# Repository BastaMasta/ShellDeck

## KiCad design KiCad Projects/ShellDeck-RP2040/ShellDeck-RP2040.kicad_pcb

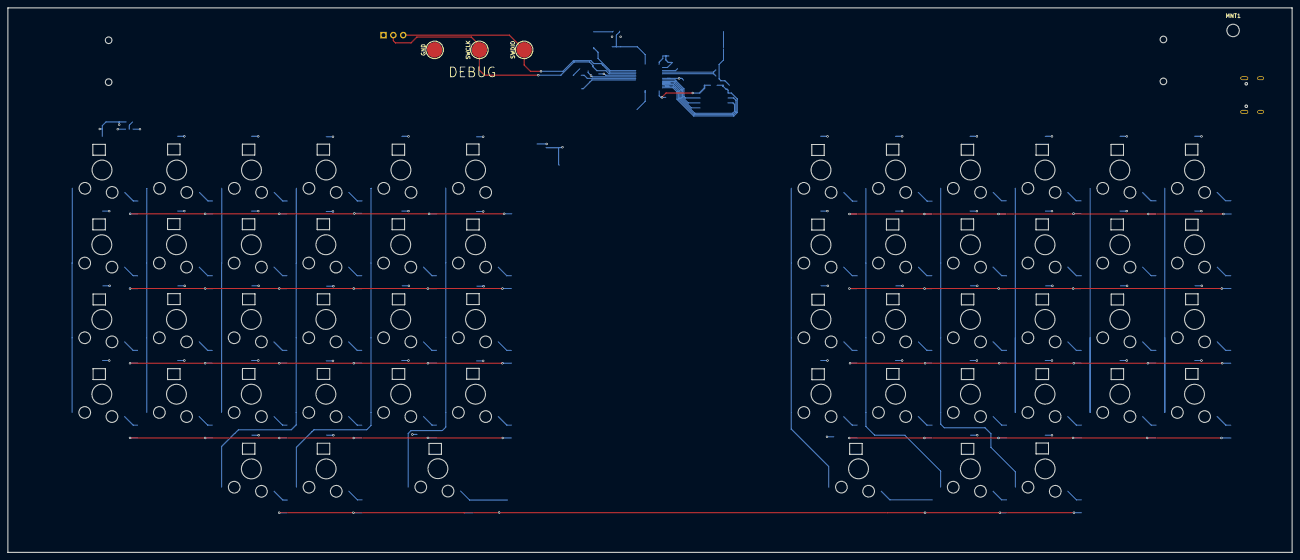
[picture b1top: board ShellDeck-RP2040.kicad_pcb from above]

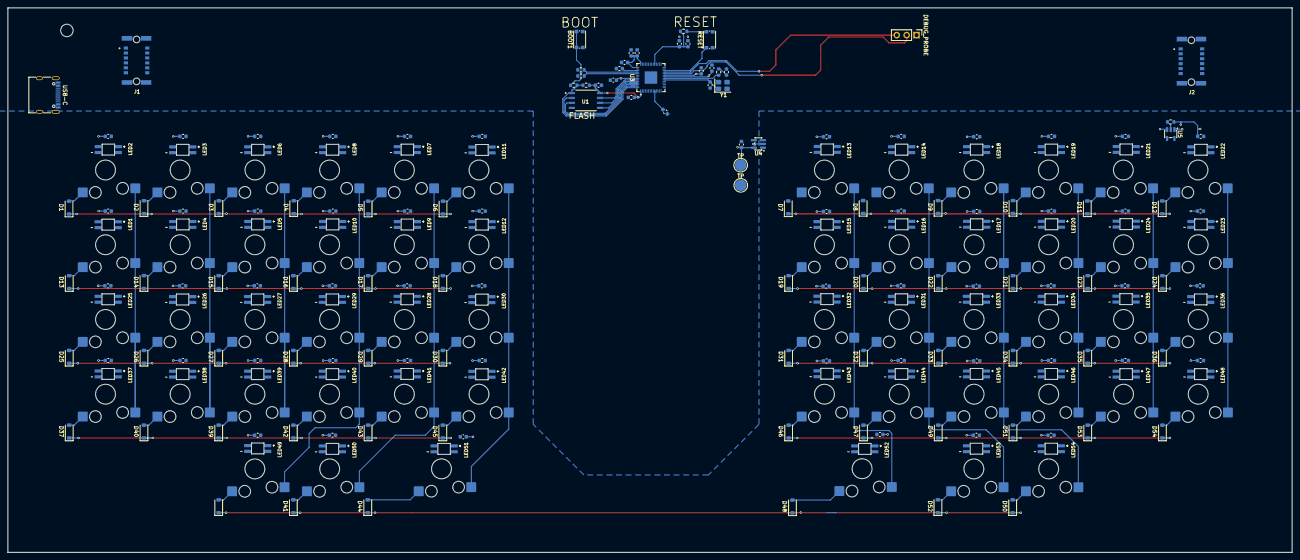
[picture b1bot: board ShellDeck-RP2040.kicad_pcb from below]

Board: 2 copper layers, 330.0 x 139.9 mm, 255 parts (251 on the bottom side), 39 nets.

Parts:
BOOT1: SW_Push_1P1T-KMR2; SW_Push_1P1T_NO_CK_KMR2
C1, C2, C3, C4, C9, C10, C12, C14, C15, C16, C17, C19: 0.1uF; C_0603_1608Metric
C12#2: 15pF; C_0603_1608Metric
C20: 12pF; C_0603_1608Metric
C21, C22, C23, C24, C25, C26, C27, C28, C29, C30, C31, C32, C33, C34, C35, C36, C37, C38, C39, C40, C41, C42, C43, C44, C45, C46, C47, C48, C49, C50, C51, C52, C53, C54, C55, C56, C57, C58, C59, C60, C61, C62, C63, C64, C65, C66, C67, C68, C69, C70, C71, C72, C73, C74, C75: C_0603; C_0603_1608Metric
D1, D2, D3, D4, D5, D6, D7, D8, D9, D10, D11, D12, D13, D14, D15, D16, D17, D18, D19, D20, D21, D22, D23, D24, D25, D26, D27, D28, D29, D30, D31, D32, D33, D34, D35, D36, D37, D38, D39, D40, D41, D42, D43, D44, D45, D46, D47, D48, D49, D50, D51, D52, D53, D54: 1N4148W; D_SOD-123
DEBUG_PROBE: PinHeader_1x03_P2.54mm_Vertical
GND: TestPoint_Pad_D4.0mm
J1, J2: M55-6001242R; HARWIN_M55-6001242R_vf.oMBanTfeTFaffFJxKZthsg
LED1, LED2, LED3, LED4, LED5, LED6, LED7, LED8, LED9, LED10, LED11, LED12, LED13, LED14, LED15, LED16, LED17, LED18, LED19, LED20, LED21, LED22, LED23, LED24, LED25, LED26, LED27, LED28, LED29, LED30, LED31, LED32, LED33, LED34, LED35, LED36, LED37, LED38, LED39, LED40, LED41, LED42, LED43, LED44, LED45, LED46, LED47, LED48, LED49, LED50, LED51, LED52, LED53, LED54: SK6812-EJ; LED_SK6812-E_vf.Ervw3JzPTGmCGe0GRPVqiQ
MNT1: MountingHole_3.2mm_M3_DIN965
R1, R4, R8: R_0603; R_0603_1608Metric
R2, R6: 1K; R_0603_1608Metric
R3, R5: 10K; R_0603_1608Metric
RESET: SW_Push_1P1T-KMR2; SW_Push_1P1T_NO_CK_KMR2
SW1, SW2, SW3, SW4, SW5, SW6, SW7, SW8, SW9, SW10, SW11, SW12, SW13, SW14, SW15, SW16, SW17, SW18, SW19, SW20, SW21, SW22, SW23, SW24, SW25, SW26, SW27, SW28, SW29, SW30, SW31, SW32, SW33, SW34, SW35, SW36, SW37, SW38, SW39, SW40, SW41, SW42, SW43, SW44, SW45, SW46, SW47, SW48, SW49, SW50, SW53, SW54: 1U; Gateron-KS33-Hotswap-1U
SW52, SW52#2: 2U; Gateron-KS33-Hotswap-2U
SWCLK: TestPoint_Pad_D4.0mm
SWDIO: TestPoint_Pad_D4.0mm
TP: TestPoint_Pad_D3.0mm
TP#2: TestPoint_Pad_D3.0mm
U1: W25Q128JVSIM_TR; SOIC127P790X216-8N_vf.sZCPWVPXQH2F8wQTRRFyVA
U3: QFN-56-1EP_7x7mm_P0.4mm_EP3.2x3.2mm
U4: AP2112K-3.3TRG1; SC-74A-5_1.55x2.9mm_P0.95mm
U5: SOT-23-5
USB-C: USB_C_Receptacle_G-Switch_GT-USB-7010ASV
Y1: Crystal_SMD_Abracon_ABM8G-4Pin_3.2x2.5mm

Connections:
+1V1: C1.1, C3.1, C9.1, U3.23, U3.45, U3.50
+3V3: C2.1, C4.1, C10.1, C12.1, C14.1, C15.1, C16.1, C17.1, C19.1, C33.1, R3.1, R5.2, TP#2.TP, U1.8, U3.1, U3.10, U3.22, U3.33, U3.42, U3.43, U3.44, U4.5
+5V: C21.1, C22.1, C23.1, C24.1, C25.1, C26.1, C27.1, C28.1, C29.1, C30.1, C31.1, C32.1, C34.1, C35.1, C36.1, C37.1, C38.1, C39.1, C40.1, C41.1, C42.1, C43.1, C44.1, C45.1, C46.1, C47.1, C48.1, C49.1, C50.1, C51.1, C52.1, C53.1, C54.1, C55.1, C56.1, C57.1, C58.1, C59.1, C60.1, C61.1, C62.1, C63.1, C64.1, C65.1, C66.1, C67.1, C68.1, C69.1, C70.1, C71.1, C72.1, C73.1, C74.1, C75.1, LED1.1, LED2.1, LED3.1, LED4.1, LED5.1, LED6.1, LED7.1, LED8.1, LED9.1, LED10.1, LED11.1, LED12.1, LED13.1, LED14.1, LED15.1, LED16.1, LED17.1, LED18.1, LED19.1, LED20.1, LED21.1, LED22.1, LED23.1, LED24.1, LED25.1, LED26.1, LED27.1, LED28.1, LED29.1, LED30.1, LED31.1, LED32.1, LED33.1, LED34.1, LED35.1, LED36.1, LED37.1, LED38.1, LED39.1, LED40.1, LED41.1, LED42.1, LED43.1, LED44.1, LED45.1, LED46.1, LED47.1, LED48.1, LED49.1, LED50.1, LED51.1, LED52.1, LED53.1, LED54.1, U4.1, U4.3, U5.5
/QSPI_SCLK: U1.6, U3.52
/QSPI_SD1: U1.2, U3.55
/QSPI_SD2: U1.3, U3.54
/QSPI_SD3: U1.7, U3.51
/QSPI_SS: R2.2, R3.2, U1.1, U3.56
COL0: SW11.1, SW33.1, SW36.1, SW47.1
COL1: SW12.1, SW34.1, SW35.1, SW48.1
COL2: SW10.1, SW31.1, SW32.1, SW46.1
COL3: SW9.1, SW29.1, SW30.1, SW45.1, SW54.1
COL4: SW7.1, SW26.1, SW28.1, SW43.1, SW53.1
COL5: SW8.1, SW25.1, SW27.1, SW44.1, SW52#2.1
COL6: SW6.1, SW23.1, SW24.1, SW42.1, SW52.1
COL7: SW4.1, SW19.1, SW22.1, SW41.1, SW50.1
COL8: SW5.1, SW20.1, SW21.1, SW40.1, SW49.1
COL9: SW3.1, SW17.1, SW18.1, SW39.1
COL10: SW2.1, SW15.1, SW16.1, SW38.1
COL11: SW1.1, SW13.1, SW14.1, SW37.1
GND: BOOT1.2, C1.2, C2.2, C3.2, C4.2, C9.2, C10.2, C12.2, C12#2.2, C14.2, C15.2, C16.2, C17.2, C19.2, C20.2, C21.2, C22.2, C23.2, C24.2, C25.2, C26.2, C27.2, C28.2, C29.2, C30.2, C31.2, C32.2, C33.2, C34.2, C35.2, C36.2, C37.2, C38.2, C39.2, C40.2, C41.2, C42.2, C43.2, C44.2, C45.2, C46.2, C47.2, C48.2, C49.2, C50.2, C51.2, C52.2, C53.2, C54.2, C55.2, C56.2, C57.2, C58.2, C59.2, C60.2, C61.2, C62.2, C63.2, C64.2, C65.2, C66.2, C67.2, C68.2, C69.2, C70.2, C71.2, C72.2, C73.2, C74.2, C75.2, DEBUG_PROBE.1, GND.TP, LED1.3, LED2.3, LED3.3, LED4.3, LED5.3, LED6.3, LED7.3, LED8.3, LED9.3, LED10.3, LED11.3, LED12.3, LED13.3, LED14.3, LED15.3, LED16.3, LED17.3, LED18.3, LED19.3, LED20.3, LED21.3, LED22.3, LED23.3, LED24.3, LED25.3, LED26.3, LED27.3, LED28.3, LED29.3, LED30.3, LED31.3, LED32.3, LED33.3, LED34.3, LED35.3, LED36.3, LED37.3, LED38.3, LED39.3, LED40.3, LED41.3, LED42.3, LED43.3, LED44.3, LED45.3, LED46.3, LED47.3, LED48.3, LED49.3, LED50.3, LED51.3, LED52.3, LED53.3, LED54.3, R8.1, RESET.2, TP.TP, U1.4, U3.19, U4.2, U5.1, U5.3, Y1.2, Y1.4
unnamed: C20.1, R6.1, Y1.3
QSPI_SD0: U1.5, U3.53
RGB: R8.2, U3.28, U5.2
ROW0: D1.1 (K), D2.1 (K), D3.1 (K), D4.1 (K), D5.1 (K), D6.1 (K), D7.1 (K), D8.1 (K), D9.1 (K), D10.1 (K), D11.1 (K), D12.1 (K)
ROW1: D13.1 (K), D14.1 (K), D15.1 (K), D16.1 (K), D17.1 (K), D18.1 (K), D19.1 (K), D20.1 (K), D21.1 (K), D22.1 (K), D23.1 (K), D24.1 (K)
ROW2: D25.1 (K), D26.1 (K), D27.1 (K), D28.1 (K), D29.1 (K), D30.1 (K), D31.1 (K), D32.1 (K), D33.1 (K), D34.1 (K), D35.1 (K), D36.1 (K)
ROW3: D37.1 (K), D39.1 (K), D40.1 (K), D42.1 (K), D43.1 (K), D45.1 (K), D46.1 (K), D47.1 (K), D49.1 (K), D51.1 (K), D53.1 (K), D54.1 (K)
ROW4: D38.1 (K), D41.1 (K), D44.1 (K), D48.1 (K), D50.1 (K), D52.1 (K)
SWCLK: DEBUG_PROBE.2, SWCLK.TP, U3.24
SWDIO: DEBUG_PROBE.3, SWDIO.TP, U3.25
USB+: J1.B6, R4.2
USB-: J1.B5, R1.2
USB_D+: R4.1, U3.47
USB_D-: R1.1, U3.46
XIN: C12#2.1, U3.20, Y1.1
XOUT: R6.2, U3.21
~BOOT: BOOT1.1, R2.1
~RESET: RESET.1, U3.26

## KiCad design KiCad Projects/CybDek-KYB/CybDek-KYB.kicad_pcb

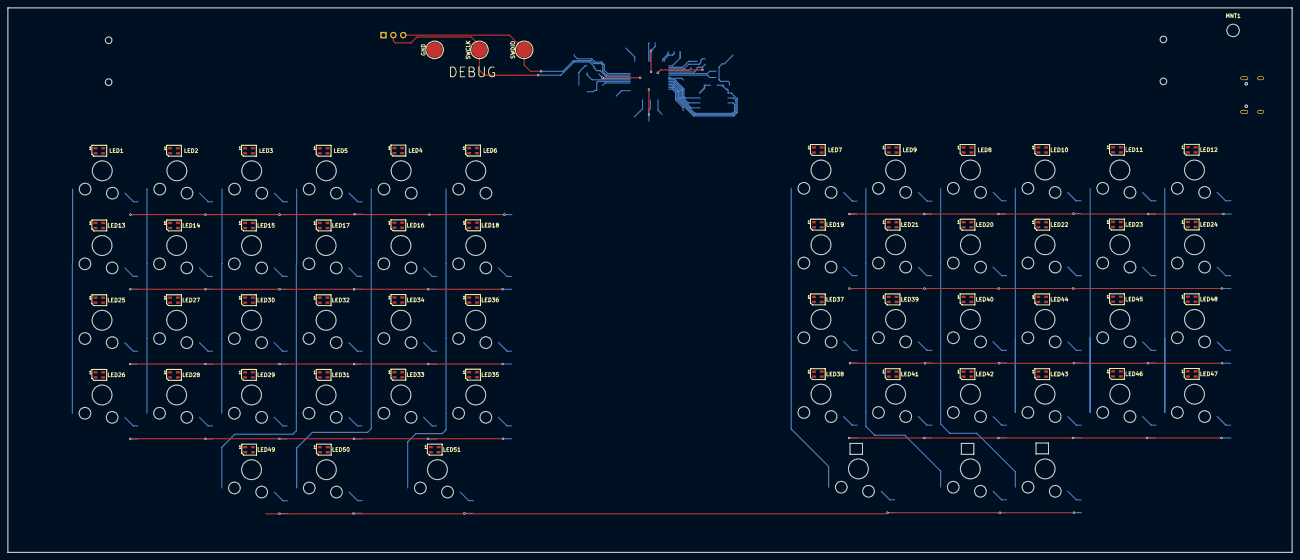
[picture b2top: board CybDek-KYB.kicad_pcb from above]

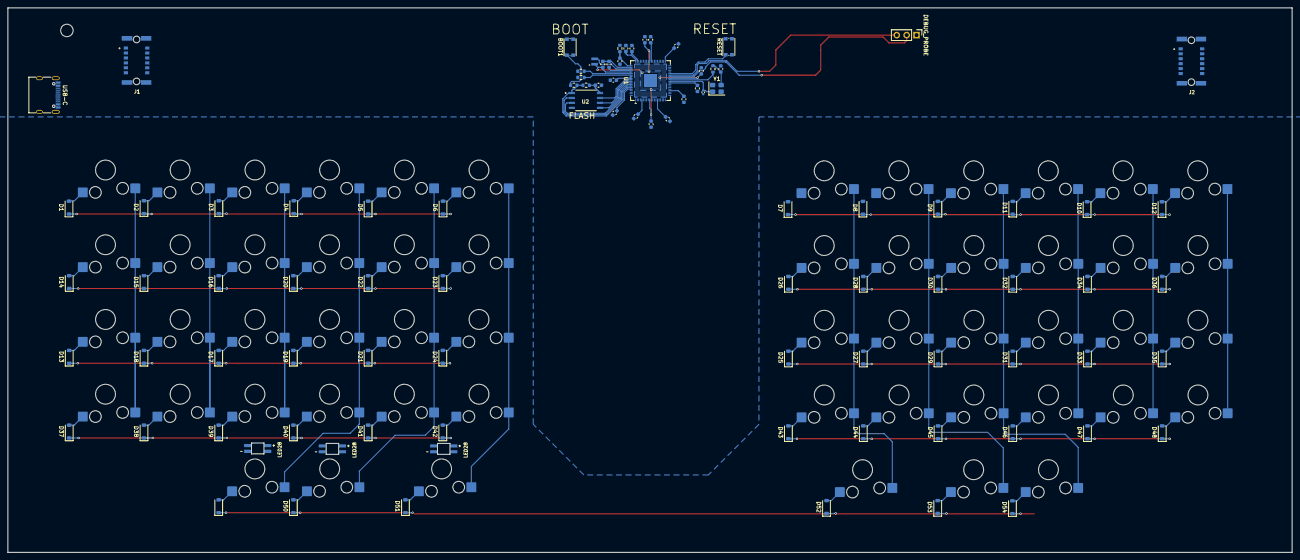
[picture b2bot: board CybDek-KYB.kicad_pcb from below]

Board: 2 copper layers, 330.0 x 139.9 mm, 201 parts (146 on the bottom side), 40 nets.

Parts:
BOOT1: SW_Push_1P1T-KMR2; SW_Push_1P1T_NO_CK_KMR2
C1, C2, C3, C4, C5, C6, C7, C8, C9, C10, C11, C12, C13, C14, C15, C16, C18, C19: C_0603; C_0603_1608Metric
C17: C_0402; C_0402_1005Metric
D1, D2, D3, D4, D5, D6, D7, D8, D9, D10, D11, D12, D13, D14, D15, D16, D17, D18, D19, D20, D21, D22, D23, D24, D25, D26, D27, D28, D29, D30, D31, D32, D33, D34, D35, D36, D37, D38, D39, D40, D41, D42, D43, D44, D45, D46, D47, D48, D49, D50, D51, D52, D53, D54: 1N4148W; D_SOD-123
DEBUG_PROBE: PinHeader_1x03_P2.54mm_Vertical
GND: TestPoint_Pad_D4.0mm
J1, J2: M55-6001242R; HARWIN_M55-6001242R_vf.oMBanTfeTFaffFJxKZthsg
L1: 3.3u; L_pol_2016
LED1, LED2, LED3, LED4, LED5, LED6, LED7, LED8, LED9, LED10, LED11, LED12, LED13, LED14, LED15, LED16, LED17, LED18, LED19, LED20, LED21, LED22, LED23, LED24, LED25, LED26, LED27, LED28, LED29, LED30, LED31, LED32, LED33, LED34, LED35, LED36, LED37, LED38, LED39, LED40, LED41, LED42, LED43, LED44, LED45, LED46, LED47, LED48, LED49, LED50, LED51: LED_SK6805_PLCC4_2.4x2.7mm_P1.3mm
LED28#2, LED28#3, LED28#4: SK6812-EJ; LED_SK6812-E_vf.Ervw3JzPTGmCGe0GRPVqiQ
MNT1: MountingHole_3.2mm_M3_DIN965
R1, R2, R3, R4, R5, R6: R_0603; R_0603_1608Metric
RESET: SW_Push_1P1T-KMR2; SW_Push_1P1T_NO_CK_KMR2
SW1, SW2, SW3, SW4, SW5, SW6, SW7, SW8, SW9, SW10, SW11, SW12, SW13, SW14, SW15, SW16, SW17, SW18, SW19, SW20, SW21, SW22, SW23, SW24, SW25, SW26, SW27, SW28, SW29, SW30, SW31, SW32, SW33, SW34, SW35, SW36, SW37, SW38, SW39, SW40, SW41, SW42, SW43, SW44, SW45, SW46, SW47, SW48, SW49, SW50, SW51, SW52, SW53, SW54: 1U; Gateron-KS33-Hotswap-1U
SWCLK: TestPoint_Pad_D4.0mm
SWDIO: TestPoint_Pad_D4.0mm
U1: QFN-80-1EP_10x10mm_P0.4mm_EP3.4x3.4mm
U2: W25Q128JVSIM_TR; SOIC127P790X216-8N_vf.sZCPWVPXQH2F8wQTRRFyVA
USB-C: USB_C_Receptacle_G-Switch_GT-USB-7010ASV
Y1: Crystal_SMD_Abracon_ABM8G-4Pin_3.2x2.5mm

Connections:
+1V1: C1.1, C11.1, C12.1, C18.1, L1.1, U1.10, U1.32, U1.51, U1.65
+3V3: C2.1, C3.1, C4.1, C6.1, C7.1, C8.1, C9.1, C10.1, C14.1, C15.1, C16.1, C19.1, R2.1, R5.1, U1.5, U1.15, U1.24, U1.29, U1.41, U1.50, U1.59, U1.60, U1.64, U1.68, U1.69, U1.76, U2.8
+5V: LED1.1, LED2.1, LED3.1, LED4.1, LED5.1, LED6.1, LED7.1, LED8.1, LED9.1, LED10.1, LED11.1, LED12.1, LED13.1, LED14.1, LED15.1, LED16.1, LED17.1, LED18.1, LED19.1, LED20.1, LED21.1, LED22.1, LED23.1, LED24.1, LED25.1, LED26.1, LED27.1, LED28.1, LED28#2.1, LED28#3.1, LED28#4.1, LED29.1, LED30.1, LED31.1, LED32.1, LED33.1, LED34.1, LED35.1, LED36.1, LED37.1, LED38.1, LED39.1, LED40.1, LED41.1, LED42.1, LED43.1, LED44.1, LED45.1, LED46.1, LED47.1, LED48.1, LED49.1, LED50.1, LED51.1
/QSPI_SCLK: U1.71, U2.6
/QSPI_SD1: U1.74, U2.2
/QSPI_SD2: U1.73, U2.3
/QSPI_SD3: U1.70, U2.7
/QSPI_SS: R2.2, R3.2, U1.75, U2.1
BOOT: BOOT1.1, R3.1
COL0: SW12.1, SW24.1, SW36.1, SW54.1
COL1: SW11.1, SW23.1, SW35.1, SW53.1
COL2: SW10.1, SW22.1, SW34.1, SW51.1
COL3: SW9.1, SW21.1, SW33.1, SW49.1, SW52.1
COL4: SW8.1, SW19.1, SW31.1, SW46.1, SW50.1
COL5: SW7.1, SW20.1, SW32.1, SW47.1, SW48.1
COL6: SW6.1, SW18.1, SW30.1, SW44.1, SW45.1
COL7: SW4.1, SW16.1, SW28.1, SW41.1, SW42.1
COL8: SW5.1, SW17.1, SW29.1, SW40.1, SW43.1
COL9: SW3.1, SW15.1, SW27.1, SW39.1
COL10: SW2.1, SW14.1, SW26.1, SW38.1
COL11: SW1.1, SW13.1, SW25.1, SW37.1
GND: BOOT1.2, C1.2, C2.2, C3.2, C4.2, C5.2, C6.2, C7.2, C8.2, C9.2, C10.2, C11.2, C12.2, C13.2, C14.2, C15.2, C16.2, C17.2, C18.2, C19.2, DEBUG_PROBE.1, GND.TP, LED1.3, LED2.3, LED3.3, LED4.3, LED5.3, LED6.3, LED7.3, LED8.3, LED9.3, LED10.3, LED11.3, LED12.3, LED13.3, LED14.3, LED15.3, LED16.3, LED17.3, LED18.3, LED19.3, LED20.3, LED21.3, LED22.3, LED23.3, LED24.3, LED25.3, LED26.3, LED27.3, LED28.3, LED28#2.3, LED28#3.3, LED28#4.3, LED29.3, LED30.3, LED31.3, LED32.3, LED33.3, LED34.3, LED35.3, LED36.3, LED37.3, LED38.3, LED39.3, LED40.3, LED41.3, LED42.3, LED43.3, LED44.3, LED45.3, LED46.3, LED47.3, LED48.3, LED49.3, LED50.3, LED51.3, RESET.2, U1.62, U1.81, U2.4, Y1.2, Y1.4
unnamed: C13.1, R6.1, Y1.3
QSPI_SD0: U1.72, U2.5
RESET: RESET.1, U1.35
ROW0: D1.1 (K), D2.1 (K), D3.1 (K), D4.1 (K), D5.1 (K), D6.1 (K), D7.1 (K), D8.1 (K), D9.1 (K), D10.1 (K), D11.1 (K), D12.1 (K)
ROW1: D14.1 (K), D15.1 (K), D16.1 (K), D20.1 (K), D22.1 (K), D23.1 (K), D26.1 (K), D28.1 (K), D30.1 (K), D32.1 (K), D34.1 (K), D36.1 (K)
ROW2: D13.1 (K), D17.1 (K), D18.1 (K), D19.1 (K), D21.1 (K), D24.1 (K), D25.1 (K), D27.1 (K), D29.1 (K), D31.1 (K), D33.1 (K), D35.1 (K)
ROW3: D37.1 (K), D38.1 (K), D39.1 (K), D40.1 (K), D41.1 (K), D42.1 (K), D43.1 (K), D44.1 (K), D45.1 (K), D46.1 (K), D47.1 (K), D48.1 (K)
ROW4: D49.1 (K), D50.1 (K), D51.1 (K), D52.1 (K), D53.1 (K), D54.1 (K)
SWCLK: DEBUG_PROBE.2, SWCLK.TP, U1.33
SWDIO: DEBUG_PROBE.3, SWDIO.TP, U1.34
USB+: J1.B6, R4.2
USB-: J1.B5, R1.2
USB_DM: R1.1, U1.66
USB_DP: R4.1, U1.67
VREG_AVDD: C5.1, R5.2, U1.61
VREG_LX: L1.2, U1.63
XIN: C17.1, U1.30, Y1.1
XOUT: R6.2, U1.31

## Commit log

2026-03-16 init commit
2026-03-16 moved files out of subfolder
2026-03-16 create fatherboard projects
2026-03-17 added 5v to 3v power convert and internal 3v lines
2026-03-20 created an adjusted the project with RP2040
2026-03-21 smol changes
2026-03-28 started work on the 3d models
2026-03-28 started and finished the hdmi ribbon to male converter
2026-03-28 updated schematic
